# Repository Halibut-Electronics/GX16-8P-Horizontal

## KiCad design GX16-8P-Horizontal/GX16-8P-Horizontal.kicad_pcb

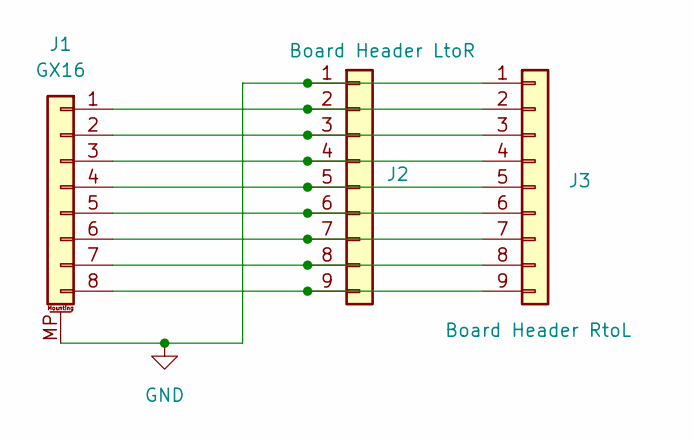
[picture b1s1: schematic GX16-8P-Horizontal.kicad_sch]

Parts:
J1: GX16; Conn_GX16-8_8pin_Aviation; Part Number GX16-F-8P
J2: Board Header LtoR; Conn_B2B-RA_2.54mm_ThroughPads_9pin_LtoR
J3: Board Header RtoL; Conn_B2B-RA_2.54mm_ThroughPads_9pin_RtoL

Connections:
GND: J1.MP (MountPin), J2.1, J3.1
unnamed: J1.1, J2.2, J3.2
unnamed: J1.2, J2.3, J3.3
unnamed: J1.3, J2.4, J3.4
unnamed: J1.4, J2.5, J3.5
unnamed: J1.5, J2.6, J3.6
unnamed: J1.6, J2.7, J3.7
unnamed: J1.7, J2.8, J3.8
unnamed: J1.8, J2.9, J3.9

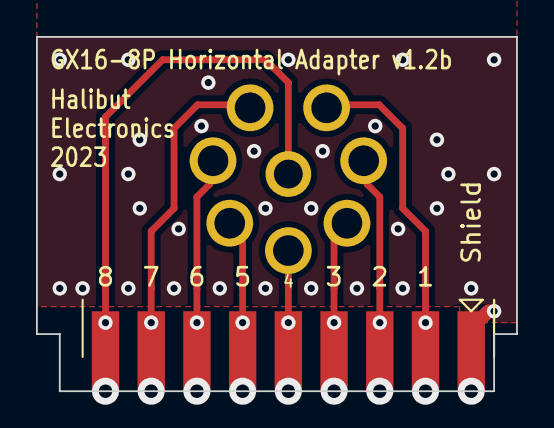
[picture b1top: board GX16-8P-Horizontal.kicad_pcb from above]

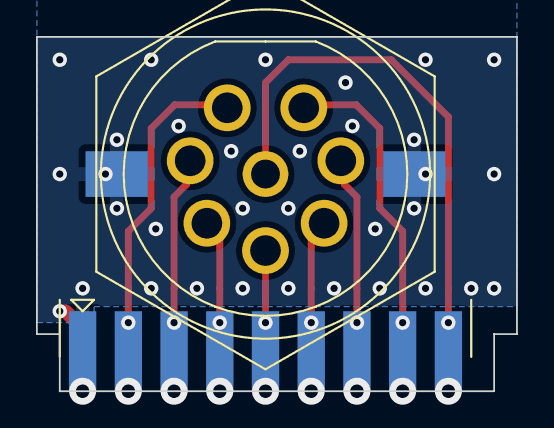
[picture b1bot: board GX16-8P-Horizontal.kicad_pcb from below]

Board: 2 copper layers, 26.7 x 19.7 mm, 3 parts (2 on the bottom side), 9 nets.

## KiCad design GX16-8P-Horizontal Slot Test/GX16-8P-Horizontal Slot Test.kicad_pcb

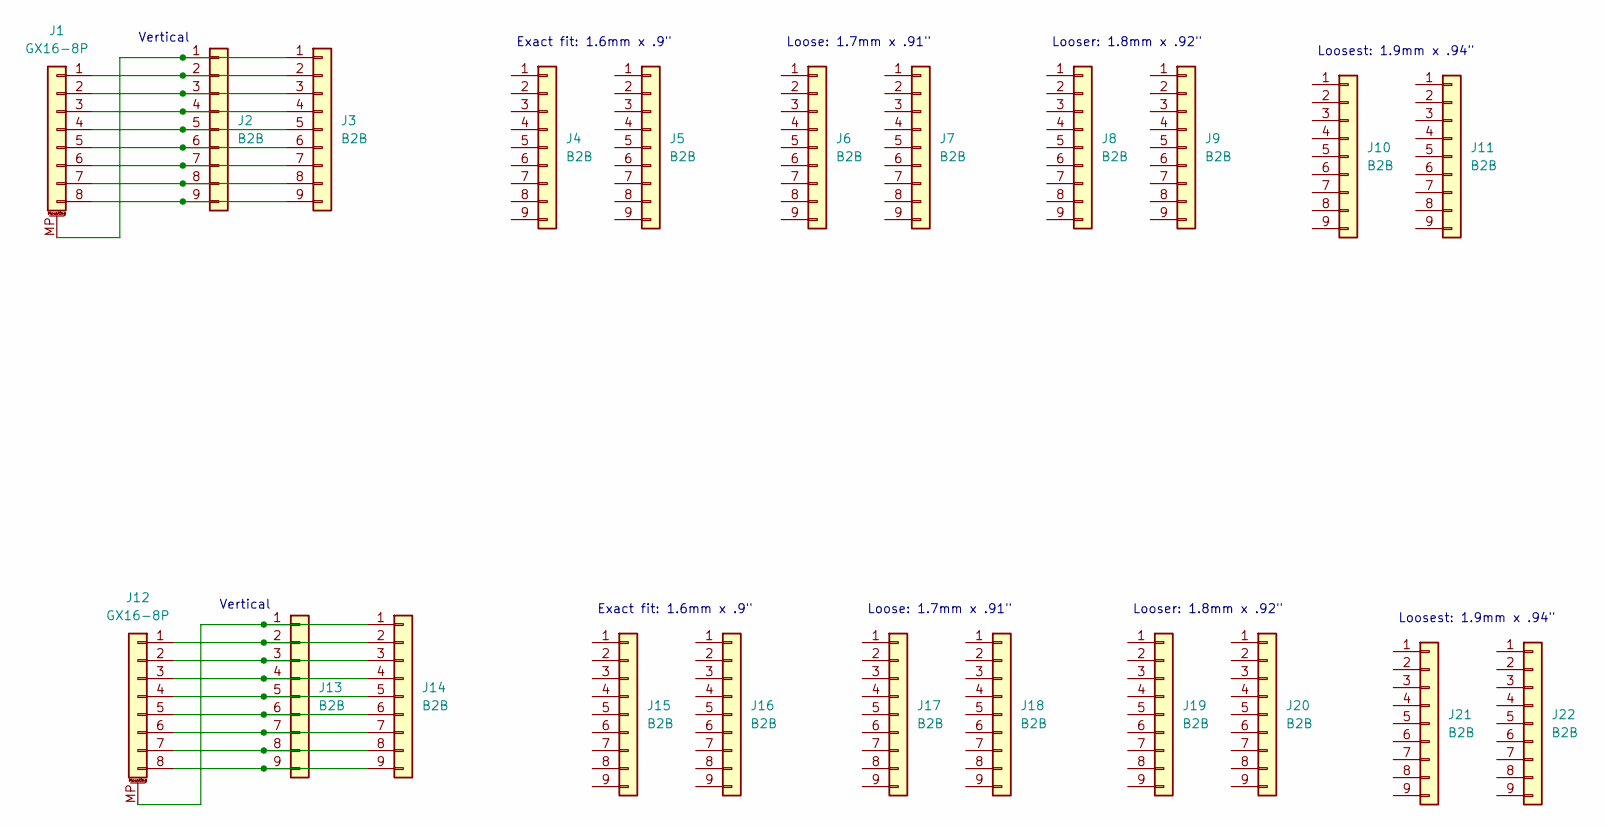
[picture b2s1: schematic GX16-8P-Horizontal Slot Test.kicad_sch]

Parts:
J1, J12: GX16-8P; Conn_GX16-8_8pin_Aviation
J2, J4, J6, J8, J10, J13, J15, J17, J19, J21: B2B; Conn_B2B-RA_2.54mm_9pin_LtoR
J3, J5, J7, J9, J11, J14, J16, J18, J20, J22: B2B; Conn_B2B-RA_2.54mm_9pin_RtoL

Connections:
unnamed: J1.1, J2.2, J3.2
unnamed: J1.2, J2.3, J3.3
unnamed: J1.3, J2.4, J3.4
unnamed: J1.4, J2.5, J3.5
unnamed: J1.5, J2.6, J3.6
unnamed: J1.6, J2.7, J3.7
unnamed: J1.7, J2.8, J3.8
unnamed: J1.8, J2.9, J3.9
unnamed: J1.MP (MountPin), J2.1, J3.1
unnamed: J12.1, J13.2, J14.2
unnamed: J12.2, J13.3, J14.3
unnamed: J12.3, J13.4, J14.4
unnamed: J12.4, J13.5, J14.5
unnamed: J12.5, J13.6, J14.6
unnamed: J12.6, J13.7, J14.7
unnamed: J12.7, J13.8, J14.8
unnamed: J12.8, J13.9, J14.9
unnamed: J12.MP (MountPin), J13.1, J14.1

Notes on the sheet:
Exact fit: 1.6mm x .9"
Loosest: 1.9mm x .94"
Looser: 1.8mm x .92"
Loose: 1.7mm x .91"
Vertical

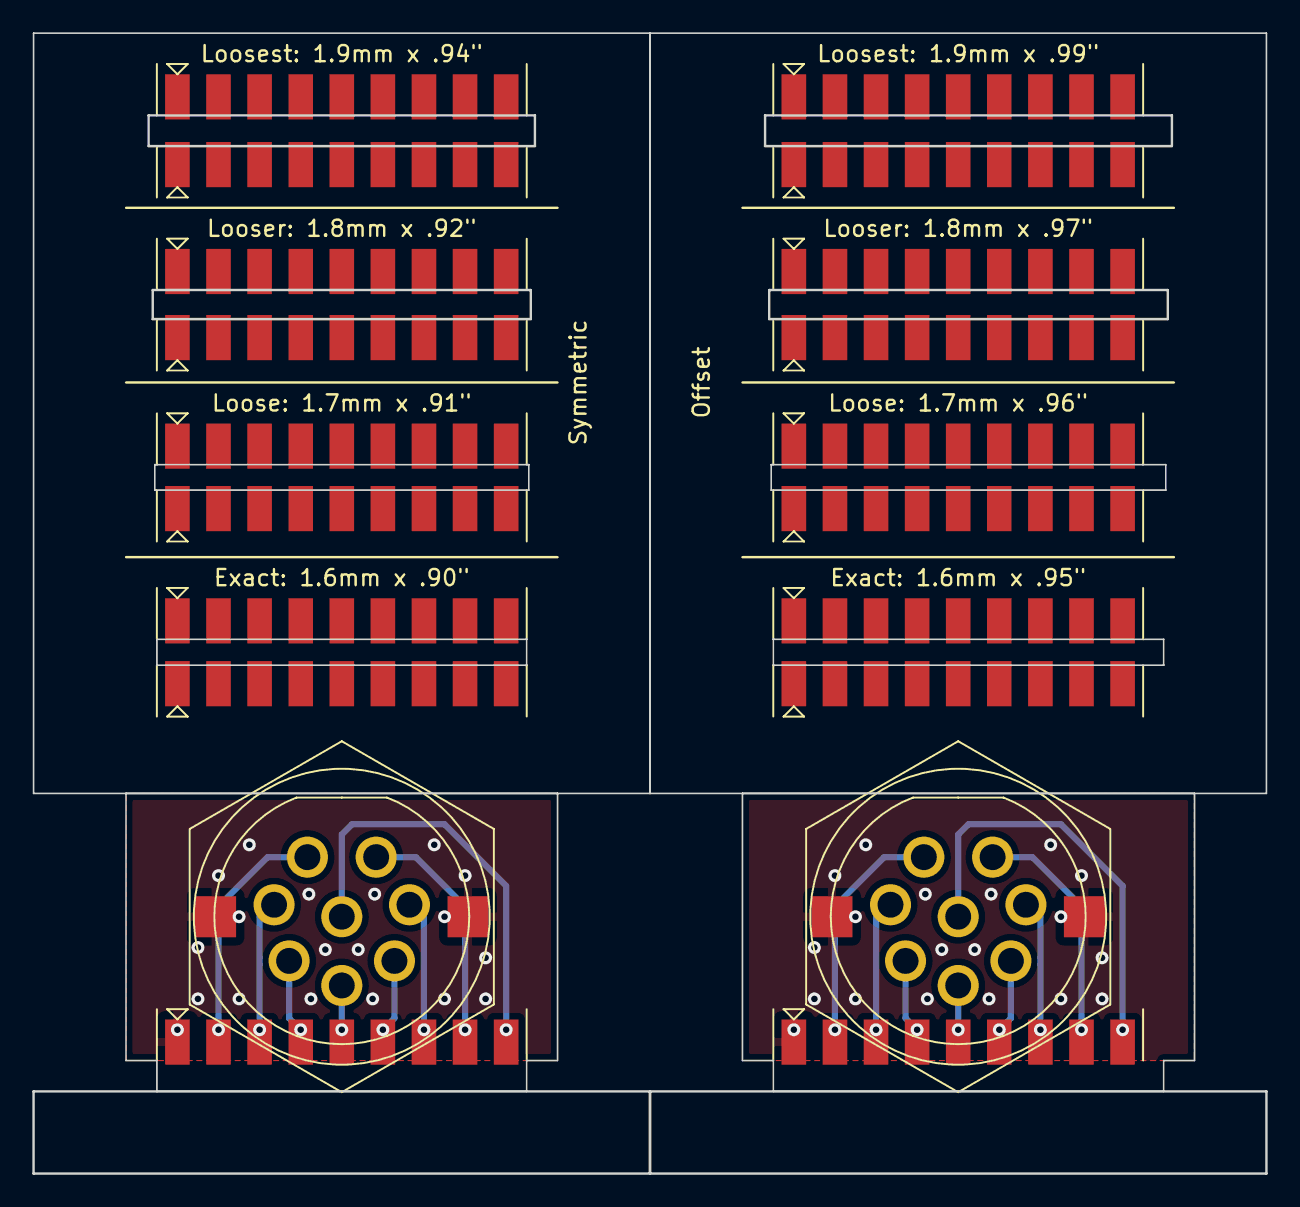
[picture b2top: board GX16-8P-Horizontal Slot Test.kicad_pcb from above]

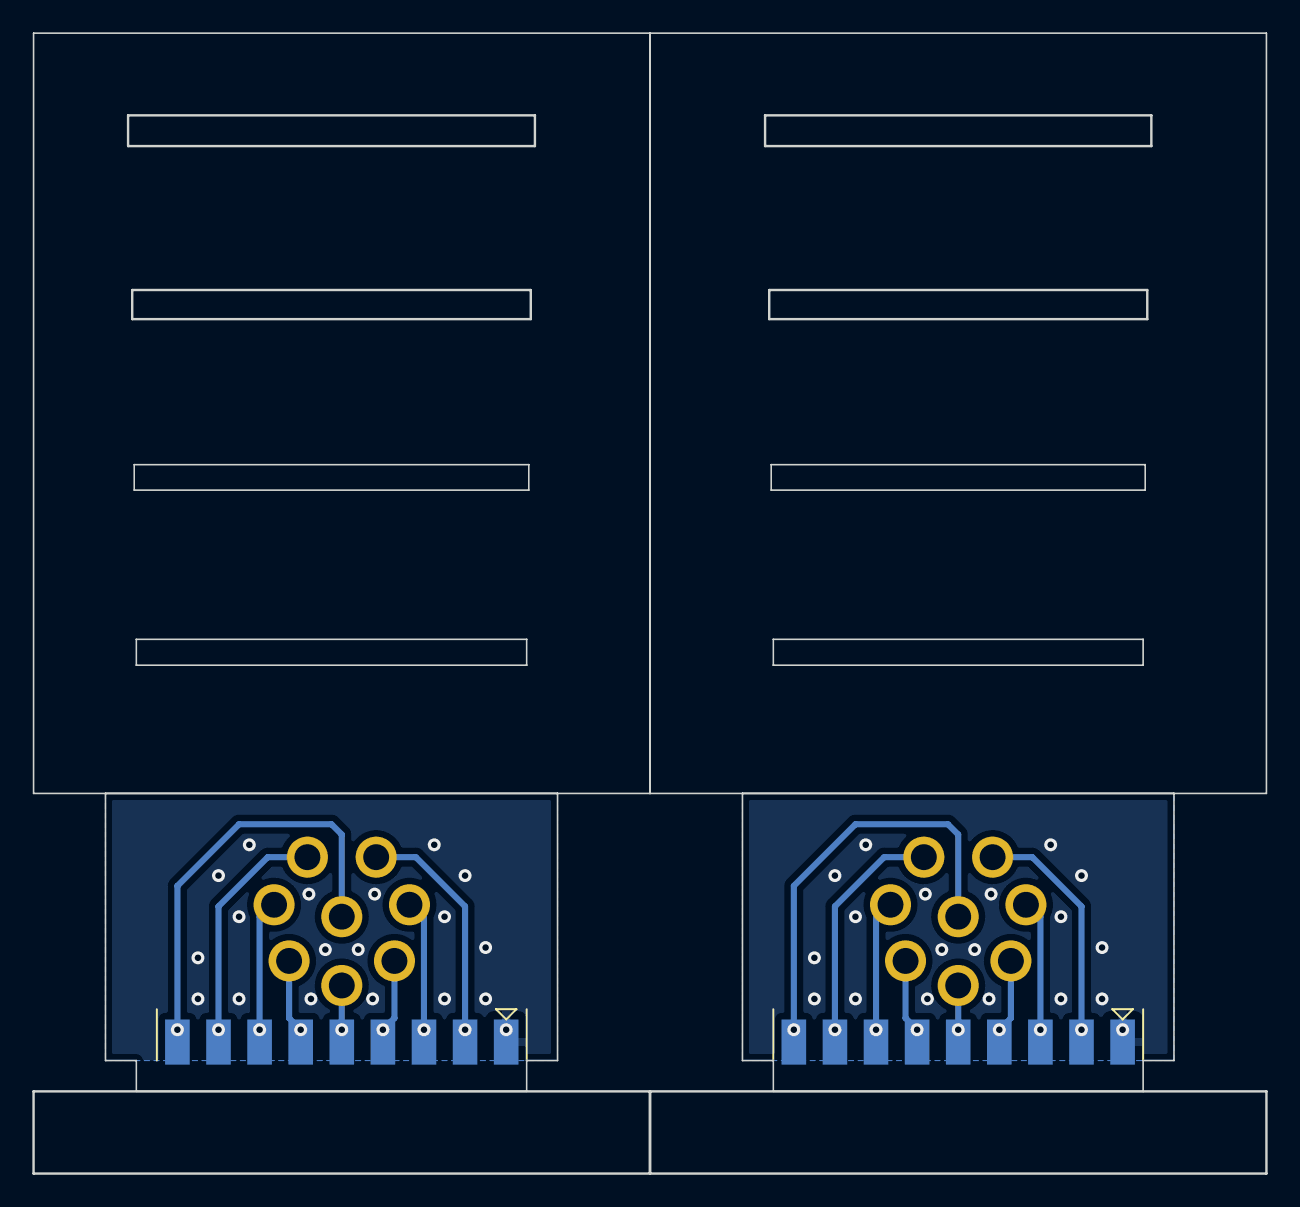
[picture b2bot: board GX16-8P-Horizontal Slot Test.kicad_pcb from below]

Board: 2 copper layers, 76.2 x 70.5 mm, 22 parts (2 on the bottom side), 18 nets.

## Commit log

2022-12-06 Empty KiCAD project. Just setting up git.
2022-12-07 Shorter GX16-8P adapter board than my previous prototypes, trying to get the connector as close to the main board as possible. Still relies on a .1" right angle header for connecting to the main boar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
2023-01-04 Updated the GX16 based on the drawing from the manufacturer. Brought pins in a bit. Wrote a python script to do the math to give me exact locations.
2023-05-25 Moving to a sub directory to make space for another board design.
2023-05-25 https://github.com/Halibut-Electronics/GX16-8P-Horizontal/issues/1 Test board for slot lengths and thicknesses
2023-05-26 https://github.com/Halibut-Electronics/HHI-Radio-Pro/issues/34 Switched from pins to card edge.
2023-06-03 https://github.com/Halibut-Electronics/HHI-User-Pro/issues/18 flip key to Pin9
2023-06-07 https://github.com/Halibut-Electronics/HHI-Radio-Pro/issues/43 Castelated the bottom edge to make soldering from the bottom easier.
2023-06-23 https://github.com/Halibut-Electronics/HHI-Radio-Pro/issues/42 As sent to Synergetics
2024-09-25 KiCAD 8
